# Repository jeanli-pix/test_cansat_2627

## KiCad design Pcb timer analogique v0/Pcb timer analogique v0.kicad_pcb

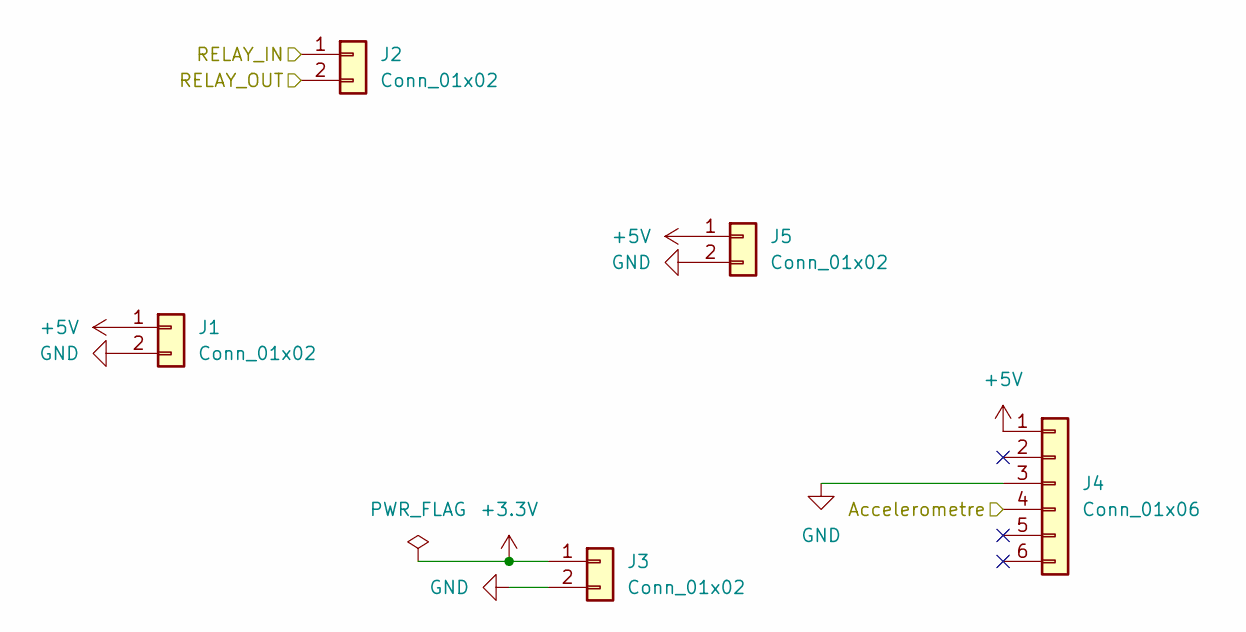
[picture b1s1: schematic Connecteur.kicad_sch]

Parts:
J1, J2, J3, J5: Conn_01x02; PinSocket_1x02_P2.54mm_Vertical_SMD_Pin1Left
J4: Conn_01x06; PinSocket_1x06_P2.54mm_Vertical_SMD_Pin1Left

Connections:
+3.3V: J3.1
+5V: J1.1, J4.1, J5.1; also elsewhere on the board
/Connecteur/Accelerometre: J4.4; also elsewhere on the board
/Connecteur/RELAY_IN: J2.1; also elsewhere on the board
/Connecteur/RELAY_OUT: J2.2; also elsewhere on the board
GND: J1.2, J3.2, J4.3, J5.2; also elsewhere on the board

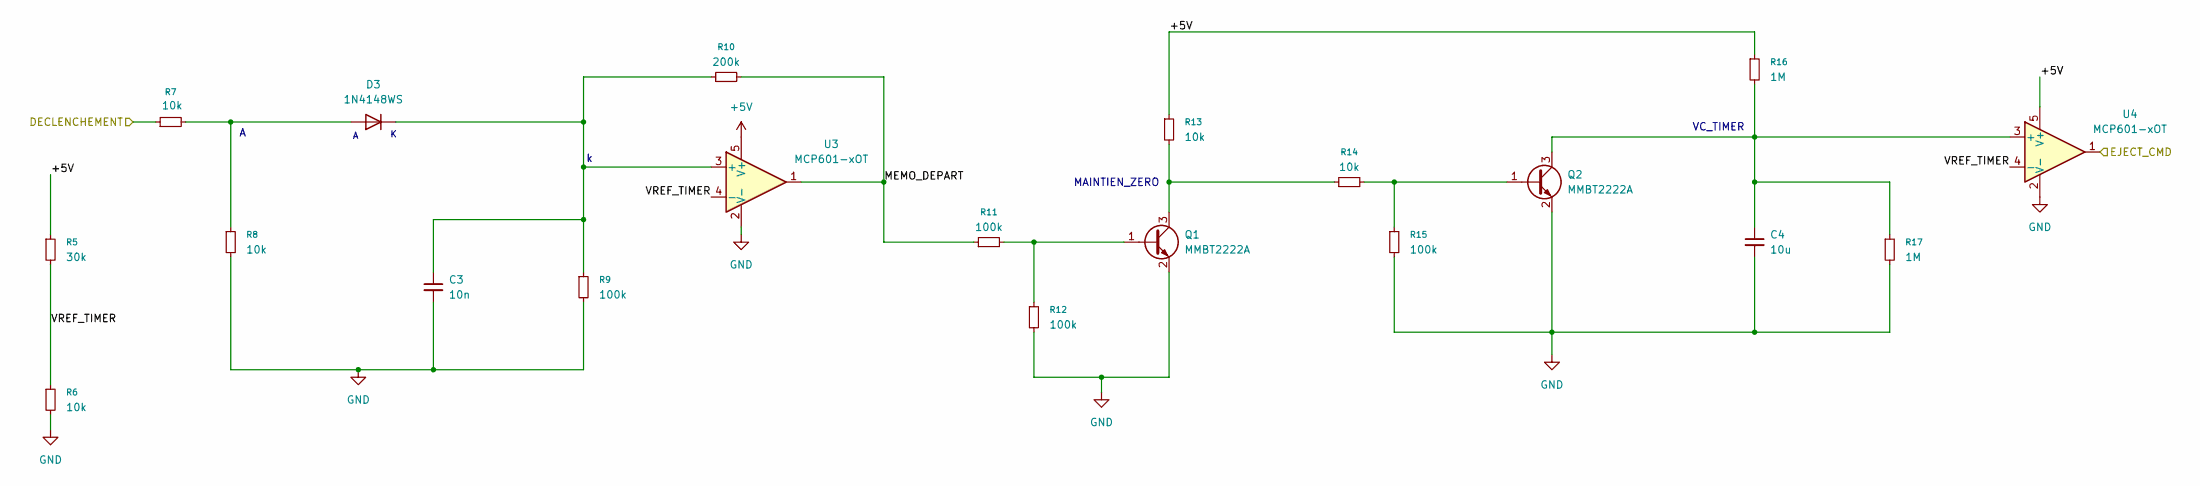
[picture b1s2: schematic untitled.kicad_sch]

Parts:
C3: 10n; C_0402_1005Metric
C4: 10u; C_0603_1608Metric
D3: 1N4148WS; D_SOD-323
Q1, Q2: MMBT2222A; SOT-23
R5: 30k; R_0402_1005Metric
R6, R7, R8, R13, R14: 10k; R_0402_1005Metric
R9, R11, R12, R15: 100k; R_0402_1005Metric
R10: 200k; R_0402_1005Metric
R16, R17: 1M; R_0402_1005Metric
U3, U4: MCP601-xOT; SOT-23-5

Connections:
+5V: R5.1, R13.1, R16.1, U3.5 (V+), U4.5 (V+); also elsewhere on the board
/Detection/DECLENCHEMENT: R7.1; also elsewhere on the board
/Puissance/EJECT_CMD: U4.1; also elsewhere on the board
/Timer/MEMO_DEPART: R10.2, R11.1, U3.1
/Timer/VREF_TIMER: R5.2, R6.1, U3.4 (-), U4.4 (-)
GND: C3.2, C4.2, Q1.2 (E), Q2.2 (E), R6.2, R8.2, R9.2, R12.2, R15.2, R17.2, U3.2 (V-), U4.2 (V-); also elsewhere on the board
unnamed: D3.2 (A), R7.2, R8.1
unnamed: C3.1, D3.1 (K), R9.1, R10.1, U3.3 (+)
unnamed: Q1.1 (B), R11.2, R12.1
unnamed: Q1.3 (C), R13.2, R14.1
unnamed: Q2.1 (B), R14.2, R15.1
unnamed: C4.1, Q2.3 (C), R16.2, R17.1, U4.3 (+)

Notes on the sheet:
MAINTIEN_ZERO
VC_TIMER

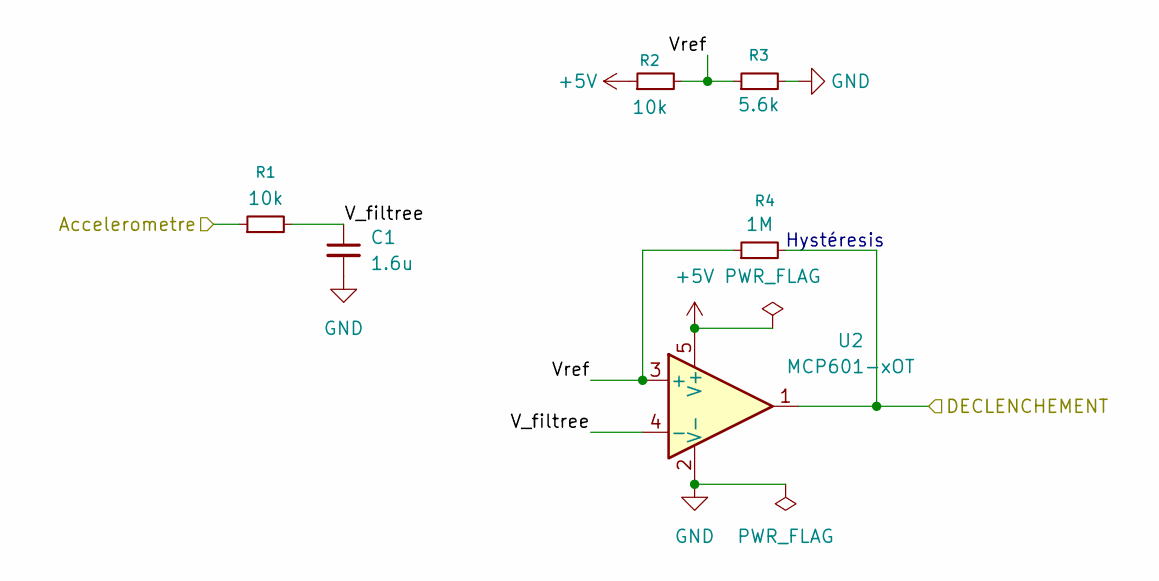
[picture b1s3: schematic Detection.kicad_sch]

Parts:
C1: 1.6u; C_0402_1005Metric
R1, R2: 10k; R_0402_1005Metric
R3: 5.6k; R_0402_1005Metric
R4: 1M; R_0402_1005Metric
U2: MCP601-xOT; SOT-23-5

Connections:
+5V: R2.1, U2.5 (V+); also elsewhere on the board
/Connecteur/Accelerometre: R1.1; also elsewhere on the board
/Detection/DECLENCHEMENT: R4.2, U2.1; also elsewhere on the board
/Detection/V_filtree: C1.1, R1.2, U2.4 (-)
/Detection/Vref: R2.2, R3.1, R4.1, U2.3 (+)
GND: C1.2, R3.2, U2.2 (V-); also elsewhere on the board

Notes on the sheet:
Hystéresis

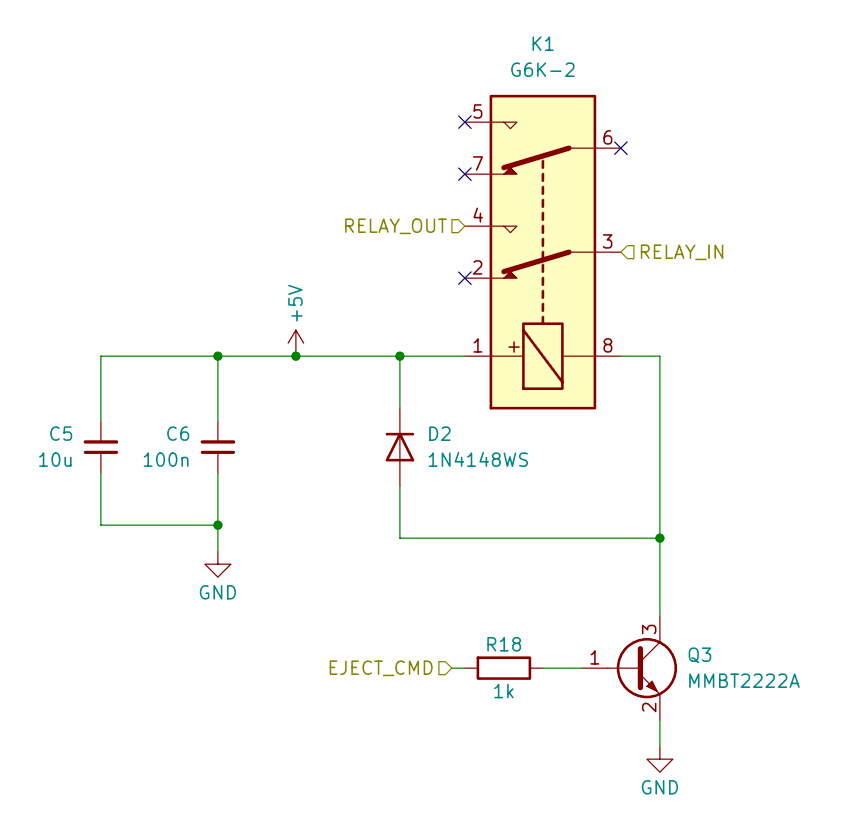
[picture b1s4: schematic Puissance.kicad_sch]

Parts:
C5: 10u; C_0603_1608Metric
C6: 100n; C_0402_1005Metric
D2: 1N4148WS; D_SOD-323
K1: G6K-2; Relay_DPDT_Omron_G6K-2F-Y
Q3: MMBT2222A; SOT-23
R18: 1k; R_0402_1005Metric

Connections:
+5V: C5.2, C6.2, D2.1 (K), K1.1; also elsewhere on the board
/Connecteur/RELAY_IN: K1.3; also elsewhere on the board
/Connecteur/RELAY_OUT: K1.4; also elsewhere on the board
/Puissance/EJECT_CMD: R18.2; also elsewhere on the board
GND: C5.1, C6.1, Q3.2 (E); also elsewhere on the board
unnamed: D2.2 (A), K1.8, Q3.3 (C)
unnamed: Q3.1 (B), R18.1

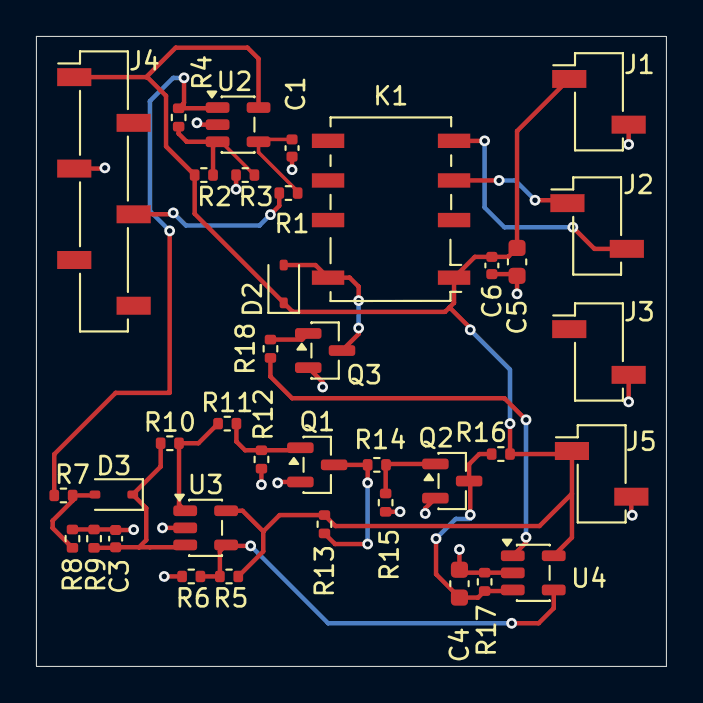
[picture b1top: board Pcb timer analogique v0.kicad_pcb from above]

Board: 4 copper layers, 35.0 x 35.0 mm, 37 parts (0 on the bottom side), 19 nets.

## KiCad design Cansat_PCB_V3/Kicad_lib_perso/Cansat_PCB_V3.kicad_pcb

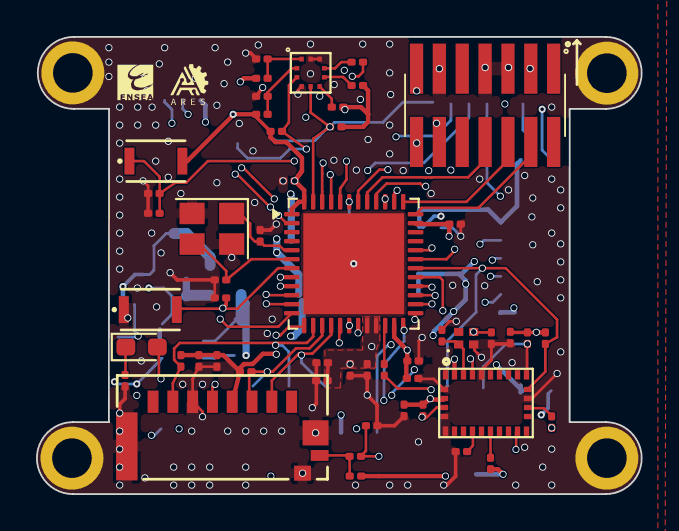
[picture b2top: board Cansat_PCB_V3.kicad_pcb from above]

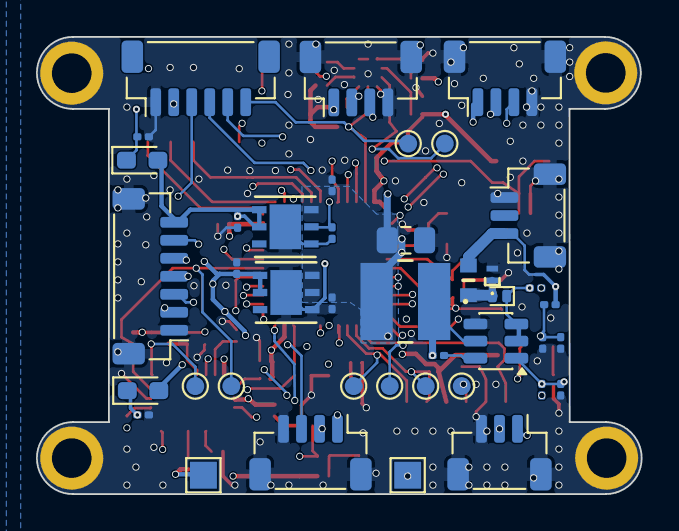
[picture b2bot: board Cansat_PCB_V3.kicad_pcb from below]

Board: 6 copper layers, 33.6 x 25.4 mm, 96 parts (41 on the bottom side), 63 nets.

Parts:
C1, C18: 4.7u; C_0201_0603Metric
C2, C3, C4, C7, C9, C12, C16, C19, C24: 100n; C_0201_0603Metric
C5, C14, C20: 10n; C_0201_0603Metric
C6, C8, C17, C25, C26, C27, C28: 1u; C_0201_0603Metric
C10, C34: 0.1u; C_0201_0603Metric
C11, C13: 16p; C_0201_0603Metric
C15: 120n; C_0201_0603Metric
C29, C30: 22p; C_0201_0603Metric
C33: 2.2u; C_0201_0603Metric
C35: 22u; C_0805_2012Metric_Pad1.18x1.45mm_HandSolder
D1, D2, D3: LED; LED_0603_1608Metric_Pad1.05x0.95mm_HandSolder
D4: Schottky; D_SOD-882D
D5: TVS; SPHV1501ETG
F1: Littel fuse 435 1.25A; FUSC1608X43N
H1, H2, H3, H4: MountingHole_Pad; MountingHole_2.2mm_M2_ISO7380_Pad
IC1: Alim STM Baro GPS IMU; DFN6_3X3_STM
IC2: Alim LoRa; DFN6_3X3_STM
J1: Lecteur SD; CONN12_47309-2651_MOL
J2: Connecteur Batterie; JST_SH_BM03B-SRSS-TB_1x03-1MP_P1.00mm_Vertical
J3: Connecteur STLINK; FTSH-107-XX-YYY-DV-K
J4: Connecteur Moteur; JST_SH_BM03B-SRSS-TB_1x03-1MP_P1.00mm_Vertical
J5: Connecteur TOF; JST_SH_BM04B-SRSS-TB_1x04-1MP_P1.00mm_Vertical
J6: Connecteur GPS; JST_SH_BM04B-SRSS-TB_1x04-1MP_P1.00mm_Vertical
J7: Connecteur LoRa; JST_SH_BM07B-SRSS-TB_1x07-1MP_P1.00mm_Vertical
J9: Connecteur Camera; JST_SH_BM04B-SRSS-TB_1x04-1MP_P1.00mm_Vertical
J10: Connecteur IHM; JST_SH_BM06B-SRSS-TB_1x06-1MP_P1.00mm_Vertical
L1: 4.7u; IND_WE-MAPI_4020_WRE
R1, R2: 10R; R_0201_0603Metric
R3: 0R; R_0201_0603Metric
R4, R6, R9, R13, R14, R17, R18, R21: 10k; R_0201_0603Metric
R5, R8, R10, R11, R12: 2.2k; R_0201_0603Metric
R7: 1.1k; R_0201_0603Metric
R15, R16: 47k; R_0201_0603Metric
R19: 20k; R_0201_0603Metric
R23, R24: 1k; R_0201_0603Metric
R25: 100k; R_0201_0603Metric
R26: 330; R_0201_0603Metric
R27: 10.2k; R_0201_0603Metric
R28: 53.6k; R_0201_0603Metric
SW1: RSTBTN; KXT 321 LHS_CNK
SW2: boot; KXT 321 LHS_CNK
TP1, TP2, TP3, TP6, TP7, TP8, TP9, TP10: TestPoint; TestPoint_Pad_D1.0mm
TP4, TP5: TestPoint; TestPoint_Pad_1.5x1.5mm
U1: Barometre BMP581; BMP581
U2: STM32G431CBUx; QFN-48-1EP_7x7mm_P0.5mm_EP5.6x5.6mm
U3: IMU BNO055; LGA28R50P4X10_380X520X100
U5: LMR51625; SOT-23-6
Y1: Crystal_GND24_Small; Crystal_SMD_3225-4pin_3.2x2.5mm
Y2: Oscillateur_IMU; WE-XTAL_IQXC-146

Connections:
+3.3V: C1.1, C2.2, C3.2, C4.2, C5.2, C6.2, C8.2, C9.2, C15.2, C16.1, C18.1, C19.1, C25.1, D2.2 (A), IC1.4 (VOUT), IC1.5 (VSENSE), J1.4, J3.03, J9.1, J10.2, R1.1, R2.1, R4.1, R5.1, R6.2, R8.2, R10.2, R11.1, R12.1, R13.1, R14.1, R15.2, R16.1, R17.1, SW2.2, TP4.1, U2.1 (VBAT), U2.20 (VREF+), U2.21 (VDDA), U2.23 (VDD), U2.35 (VDD), U2.48 (VDD), U3.3 (VDD), U3.28 (VDDIO)
+3.3VEN: C28.1, D3.2 (A), IC2.4 (VOUT), IC2.5 (VSENSE), J7.7
+5V: C26.1, C27.1, C35.1, IC1.2 (EN), IC1.3 (VIN), IC2.3 (VIN), J4.2, J5.1, J6.1, L1.2, R28.2, TP5.1
ADC1_IN12_VBAT: C24.2, R19.1, R21.2, U2.18 (PB1)
DIO0_LoRa: J7.2, U2.42 (PB4)
EXTI13_BTN: J10.4, U2.2 (PC13)
EXTI_BARO: R3.2, U2.12 (PA4)
GND: C1.2, C2.1, C3.1, C4.1, C5.1, C6.1, C7.2, C8.1, C9.1, C10.1, C11.1, C12.2, C13.2, C14.1, C15.1, C16.2, C17.1, C18.2, C19.2, C20.2, C24.1, C25.2, C26.2, C27.2, C28.2, C29.2, C30.2, C33.2, C35.2, D5.2 (A), H1.1, H2.1, H3.1, H4.1, IC1.1 (GND), IC1.7 (EPAD), IC2.1 (GND), IC2.7 (EPAD), J1.6, J1.G1, J1.G2, J1.G4, J2.1, J2.MP, J3.05, J3.07, J3.11, J4.3, J4.MP, J5.4, J5.MP, J6.4, J6.MP, J7.1, J7.MP, J9.4, J9.MP, J10.1, R7.1, R9.2, R21.1, R23.1, R24.1, R25.2, R27.2, SW1.1, U1.3 (VSS_1), U1.8 (VSS_2), U1.9 (VSS_3), U2.49 (VSS), U3.2 (GND), U3.5 (PS1), U3.6 (PS0), U3.18 (COM2), U3.25 (GNDIO), U5.4 (GND), Y1.2, Y1.4, Y2.2
I2C1_SCL: J10.5, R5.2, TP1.1, U1.2 (SCK), U2.38 (PA15)
I2C1_SDA: J10.6, R8.1, TP2.1, U1.4 (SDI), U2.47 (PB9)
I2C3_SCL_IMU: R11.2, TP3.1, U2.30 (PA8), U3.19 (COM1)
I2C3_SDA_IMU: R10.1, TP6.1, U2.40 (PC11), U3.20 (COM0)
IMU_BOOT: R13.2, U2.9 (PA1), U3.4 (NBOOT_LOAD_PIN)
IMU_INT: U2.8 (PA0), U3.14 (INT)
IMU_RST: R14.2, U3.11 (NRESET)
LED_DATA: J10.3, R26.1
NRST: C10.2, J3.12, SW1.2, U2.7 (PG10)
unnamed: D1.2 (A), U2.17 (PB0)
unnamed: D1.1 (K), R7.2
unnamed: D2.1 (K), R23.2
unnamed: D3.1 (K), R24.2
unnamed: D4.2 (A), D5.1 (K), F1.2
unnamed: C33.1, D4.1 (K), U5.2 (EN), U5.3 (VIN)
unnamed: J1.G3, R17.2, R18.1
unnamed: R4.2, U1.6 (CSB)
unnamed: R3.1, U1.7 (INT)
unnamed: R6.1, U1.5 (SDO)
unnamed: C7.1, R1.2, U1.10 (VDD)
unnamed: C12.1, R2.2, U1.1 (VDDIO)
unnamed: C14.2, R9.1, SW2.1, U2.46 (PB8)
unnamed: R26.2, U2.22 (PB10)
unnamed: C11.2, U2.5 (PF0), Y1.1
unnamed: C13.1, U2.6 (PF1), Y1.3
unnamed: C17.2, U3.9 (CAP)
unnamed: R12.2, U3.17 (COM3)
unnamed: C29.1, U3.27 (XIN32), Y2.1
unnamed: C30.1, U3.26 (XOUT32), Y2.3
unnamed: C34.1, U5.6 (CB)
unnamed: R27.1, R28.1, U5.1 (FB)
unnamed: C34.2, L1.1, U5.5 (SW)
PWEN: IC2.2 (EN), R25.1, U2.43 (PB5)
SDDETECT: C20.1, R18.2, U2.19 (PB2)
SPI1_CS_SD: J1.2, TP7.1, U2.16 (PC4)
SPI1_MISO_SD: J1.7, R16.2, TP10.1, U2.14 (PA6)
SPI1_MOSI_SD: J1.3, R15.1, TP8.1, U2.15 (PA7)
SPI1_SCK_SD: J1.5, TP9.1, U2.13 (PA5)
SPI2_MISO_LoRa: J7.5, U2.27 (PB14)
SPI2_MOSI_LoRa: J7.4, U2.28 (PB15)
SPI2_NSS/CS: J7.6, U2.25 (PB12)
SPI2_SCK_LoRa: J7.3, U2.26 (PB13)
SWCLK/I2C1_SDA: J3.06, U2.37 (PA14)
SWDIO: J3.04, U2.36 (PA13)
SWO: J3.08, U2.41 (PB3)
TIM3_CHI_PWM4_MOT: J4.1, U2.29 (PC6)
USART1_RX_GPS: J6.2, U2.45 (PB7)
USART1_RX_STLINK: J3.13, U2.32 (PA10)
USART1_TX_GPS: J6.3, U2.44 (PB6)
USART1_TX_STLINK: J3.14, U2.31 (PA9)
USART2_RX_CAM: J9.2, U2.11 (PA3)
USART2_TX_CAM: J9.3, U2.10 (PA2)
USART_RX_TOF: J5.2, U2.24 (PB11)
USART_TX_TOF: J5.3, U2.39 (PC10)
VIN: F1.1, J2.3, R19.2
